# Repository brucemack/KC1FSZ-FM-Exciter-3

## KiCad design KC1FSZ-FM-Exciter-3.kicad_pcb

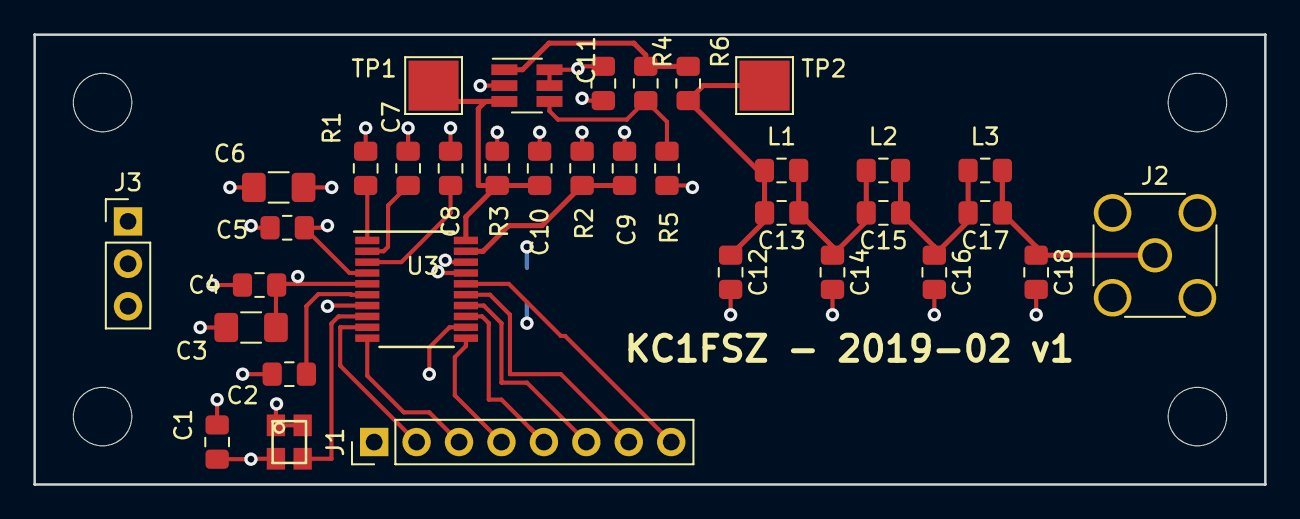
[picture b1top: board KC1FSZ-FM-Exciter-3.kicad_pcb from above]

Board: 4 copper layers, 73.7 x 26.9 mm, 36 parts (1 on the bottom side), 24 nets.

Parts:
C1, C2, C4, C5: 100nF; C_0805_2012Metric_Pad1.15x1.40mm_HandSolder
C3, C6: 10uF; C_1206_3216Metric_Pad1.42x1.75mm_HandSolder
C7, C8: 10nF; C_0805_2012Metric_Pad1.15x1.40mm_HandSolder
C9, C10: 20pf; C_0805_2012Metric_Pad1.15x1.40mm_HandSolder
C11: 0.1uF; C_0805_2012Metric_Pad1.15x1.40mm_HandSolder
C12, C13, C14, C15, C16, C17, C18: C_Small; C_0805_2012Metric_Pad1.15x1.40mm_HandSolder
FB1: Ferrite_Bead_Small; L_0805_2012Metric_Pad1.15x1.40mm_HandSolder
J1: Interface; PinHeader_1x08_P2.54mm_Vertical
J2: RF_OUT; SMA_Amphenol_132134_Vertical
J3: Power; PinHeader_1x03_P2.54mm_Vertical
L1, L2, L3: L_Small; L_0805_2012Metric_Pad1.15x1.40mm_HandSolder
R1: 6.8K; R_0805_2012Metric_Pad1.15x1.40mm_HandSolder
R2, R3: 200R; R_0805_2012Metric_Pad1.15x1.40mm_HandSolder
R4, R5: 1K; R_0805_2012Metric_Pad1.15x1.40mm_HandSolder
R6: 50R; R_0805_2012Metric_Pad1.15x1.40mm_HandSolder
TP1, TP2: TestPoint; TestPoint_Pad_3.0x3.0mm
U2: KC2520K_OSC; KYOCERA_KC2520K_HandSolder
U3: AD9834; TSSOP-20_4.4x6.5mm_P0.65mm
U4: ADA4851-1; SOT-23-6_Handsoldering

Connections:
+3.3VA: C5.1, C6.1, C8.1, C11.1, J3.2, U3.4, U4.5, U4.6
+3V3: C1.1, C3.1, C4.1, J3.3, U2.1, U2.4, U3.5
/BUFFER_OUT: R4.2, R6.2, U4.1
/FSELECT: J1.2, U3.9
/IOUT: C9.1, R2.1, U3.19
/IOUTB: C10.1, R3.1, TP1.1, U3.20, U4.3
/MCLK: U2.3, U3.8
/OUT: C17.1, C18.1, J2.1, L3.1
/PSELECT: J1.3, U3.10
GND: C1.2, C2.2, C3.2, C4.2, FB1.1, J1.1, U2.2, U3.7, U3.12
GNDA: C5.2, C6.2, C7.2, C9.2, C10.2, C11.2, C12.2, C14.2, C16.2, C18.2, FB1.2, J2.2, J3.1, R1.2, R2.2, R3.2, R5.2, U3.17, U3.18, U4.2
unnamed: C2.1, U3.6
unnamed: C7.1, U3.2
unnamed: C8.2, U3.3
unnamed: C12.1, C13.2, L1.2, R6.1, TP2.1
unnamed: C13.1, C14.1, C15.2, L1.1, L2.2
unnamed: C15.1, C16.1, C17.2, L2.1, L3.2
unnamed: J1.4, U3.11
unnamed: J1.5, U3.13
unnamed: J1.6, U3.14
unnamed: J1.7, U3.15
unnamed: R1.1, U3.1
unnamed: R4.1, R5.1, U4.4
SIGNOUT: J1.8, U3.16
